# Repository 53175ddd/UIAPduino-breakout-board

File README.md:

# UIAPduino Breakout Board

UIAPduino を使った開発を手助けする，ブレッドボード用のブレイクアウトボードです．

## 部品表

| 部品番号 | 部品名 | 定数等 | リンク |
|----|----|----|----|
| C1 | コンデンサ | 0.22uF | [108146](<https://akizukidenshi.com/catalog/g/g108146/>) |
| C2 | コンデンサ | 0.1uF | [110147](<https://akizukidenshi.com/catalog/g/g110147/>) |
| C3 | コンデンサ | 22uF | [117899](<https://akizukidenshi.com/catalog/g/g117899/>) |
| C4 | コンデンサ | 10uF | [110590](<https://akizukidenshi.com/catalog/g/g110590/>) |
| D1 | ダイオード | 1N4148 | [100941](<https://akizukidenshi.com/catalog/g/g100941/>) |
| J1 | ピンヘッダ | 20P | [116590](<https://akizukidenshi.com/catalog/g/g116590/>) |
| J2 | ピンソケット | 20P | [103077](<https://akizukidenshi.com/catalog/g/g103077/>) |
| J3 | DC ジャック | 55-25 | [106568](<https://akizukidenshi.com/catalog/g/g106568/>) |
| U1 | USB-UART 変換 | FT234X モジュール | [108461](<https://akizukidenshi.com/catalog/g/g108461/>) |
| U2 | マイコン | UIAPduino Pro Micro CH32V003 | [ssci.to/9914](<https://www.switch-science.com/products/9914>) |
| U3 | 電源レギュレータ | NJM7805 | [108678](<https://akizukidenshi.com/catalog/g/g108678/>) |

## アートワークイメージ

[KiCanvas](https://kicanvas.org) でアートワークを見ることができます．  
<https://kicanvas.org/?repo=https%3A%2F%2Fgithub.com%2F53175ddd%2FUIAPduino-breakout-board>

---

This work is licensed under <a href="https://creativecommons.org/licenses/by-sa/4.0/">CC BY-SA 4.0</a>

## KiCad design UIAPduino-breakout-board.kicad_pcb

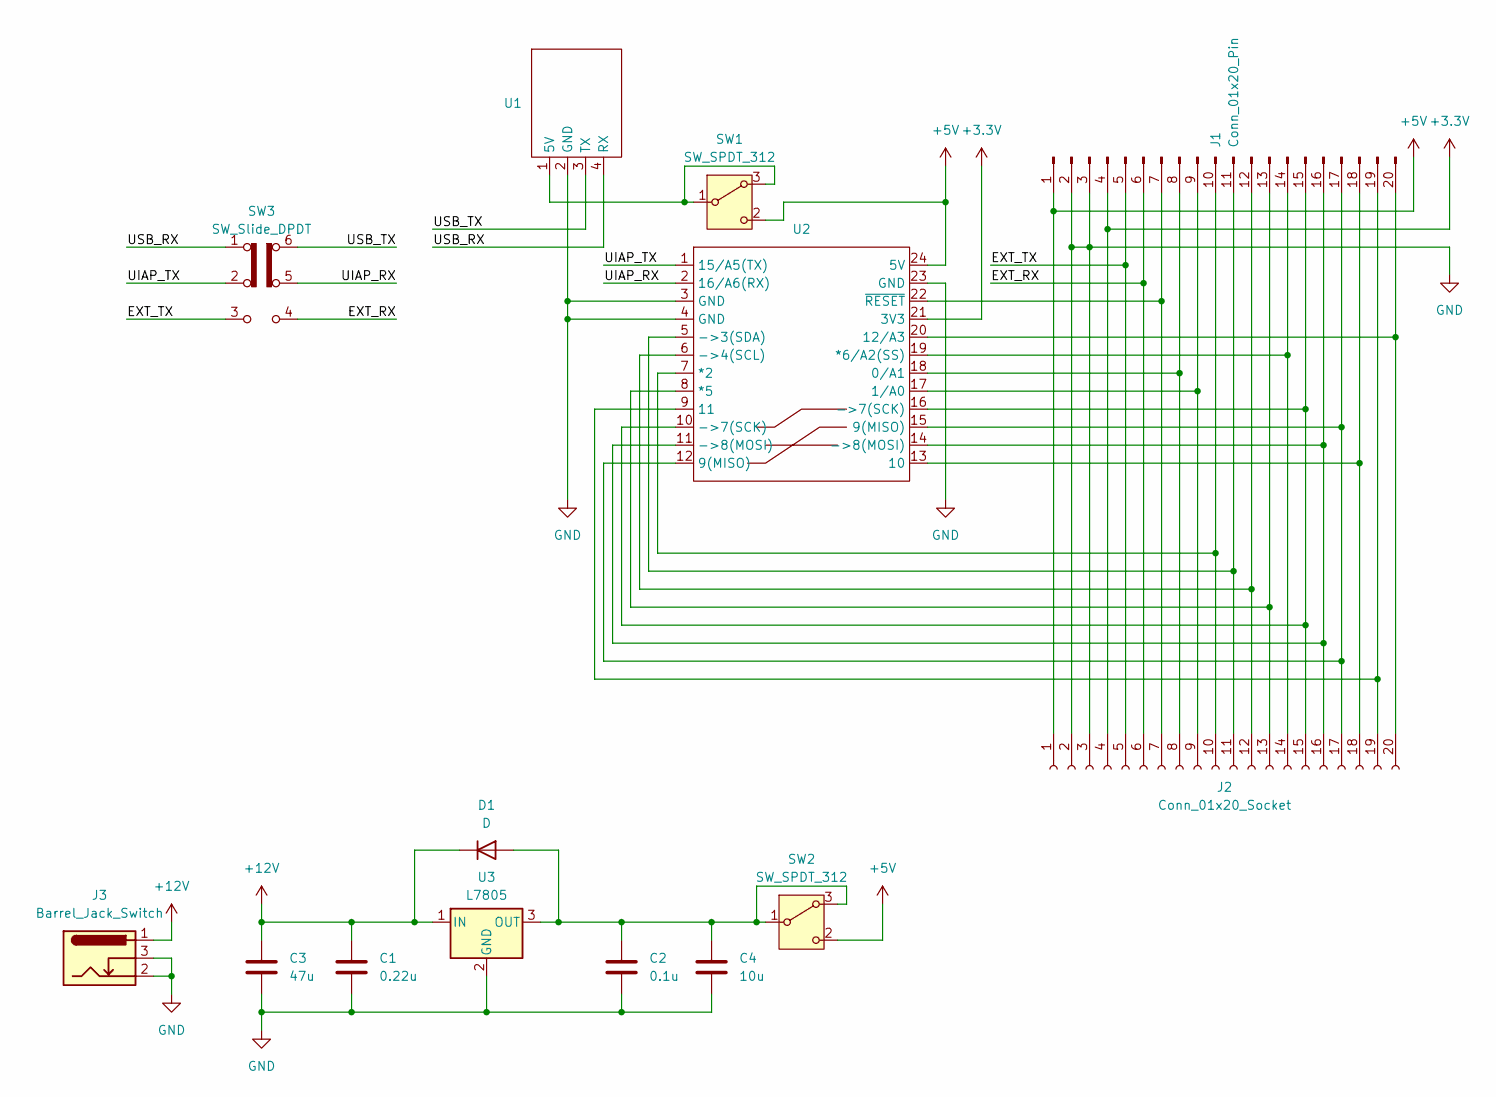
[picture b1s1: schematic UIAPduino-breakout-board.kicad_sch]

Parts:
C1: 0.22u; C_Disc_D5.0mm_W2.5mm_P5.00mm
C2: 0.1u; C_Disc_D5.0mm_W2.5mm_P5.00mm
C3: 47u; CP_Radial_D5.0mm_P2.00mm
C4: 10u; CP_Radial_D4.0mm_P1.50mm
D1: D; D_A-405_P7.62mm_Horizontal
J1: Conn_01x20_Pin; PinHeader_1x20_P2.54mm_Vertical
J2: Conn_01x20_Socket; PinSocket_1x20_P2.54mm_Vertical
J3: Barrel_Jack_Switch; BarrelJack_Horizontal
SW1, SW2: SW_SPDT_312; SW_Slide-03_Wuerth-WS-SLTV_10x2.5x6.4_P2.54mm
SW3: SW_Slide_DPDT; SW_CK_JS202011CQN_DPDT_Straight
U1: FT234X
U2: UIAPDUINO-PRO-MICRO-CH32V003-V1DOT4
U3: L7805; TO-220F-3_Vertical

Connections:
+3.3V: J1.4, J2.4, U2.21 (3V3)
+5V: J1.1, J2.1, SW1.2 (C), SW2.2 (C), U2.24 (5V)
+12V: C1.1, C3.1, D1.1 (K), J3.1, U3.1 (IN)
/EXT_RX: J1.6, J2.6, SW3.4 (A)
/EXT_TX: J1.5, J2.5, SW3.3 (C)
/UIAP_RX: SW3.5 (B), U2.2 (16/A6(RX))
/UIAP_TX: SW3.2 (B), U2.1 (15/A5(TX))
/USB_RX: SW3.1 (A), U1.4 (RX)
/USB_TX: SW3.6 (C), U1.3 (TX)
GND: C1.2, C2.2, C3.2, C4.2, J1.2, J1.3, J2.2, J2.3, J3.2, J3.3, U1.2 (GND), U2.3 (GND), U2.4 (GND), U2.23 (GND), U3.2 (GND)
unnamed: C2.1, C4.1, D1.2 (A), SW2.1 (B), SW2.3 (A), U3.3 (OUT)
unnamed: J1.7, J2.7, U2.22 (~RESET)
unnamed: J1.8, J2.8, U2.18 (0/A1)
unnamed: J1.9, J2.9, U2.17 (1/A0)
unnamed: J1.10, J2.10, U2.7 (*2)
unnamed: J1.11, J2.11, U2.5 (->3(SDA))
unnamed: J1.12, J2.12, U2.6 (->4(SCL))
unnamed: J1.13, J2.13, U2.8 (*5)
unnamed: J1.14, J2.14, U2.19 (*6/A2(SS))
unnamed: J1.15, J2.15, U2.10 (->7(SCK)), U2.16 (->7(SCK))
unnamed: J1.16, J2.16, U2.11 (->8(MOSI)), U2.14 (->8(MOSI))
unnamed: J1.17, J2.17, U2.12 (9(MISO)), U2.15 (9(MISO))
unnamed: J1.18, J2.18, U2.13 (10)
unnamed: J1.19, J2.19, U2.9 (11)
unnamed: J1.20, J2.20, U2.20 (12/A3)
unnamed: SW1.1 (B), SW1.3 (A), U1.1 (5V)

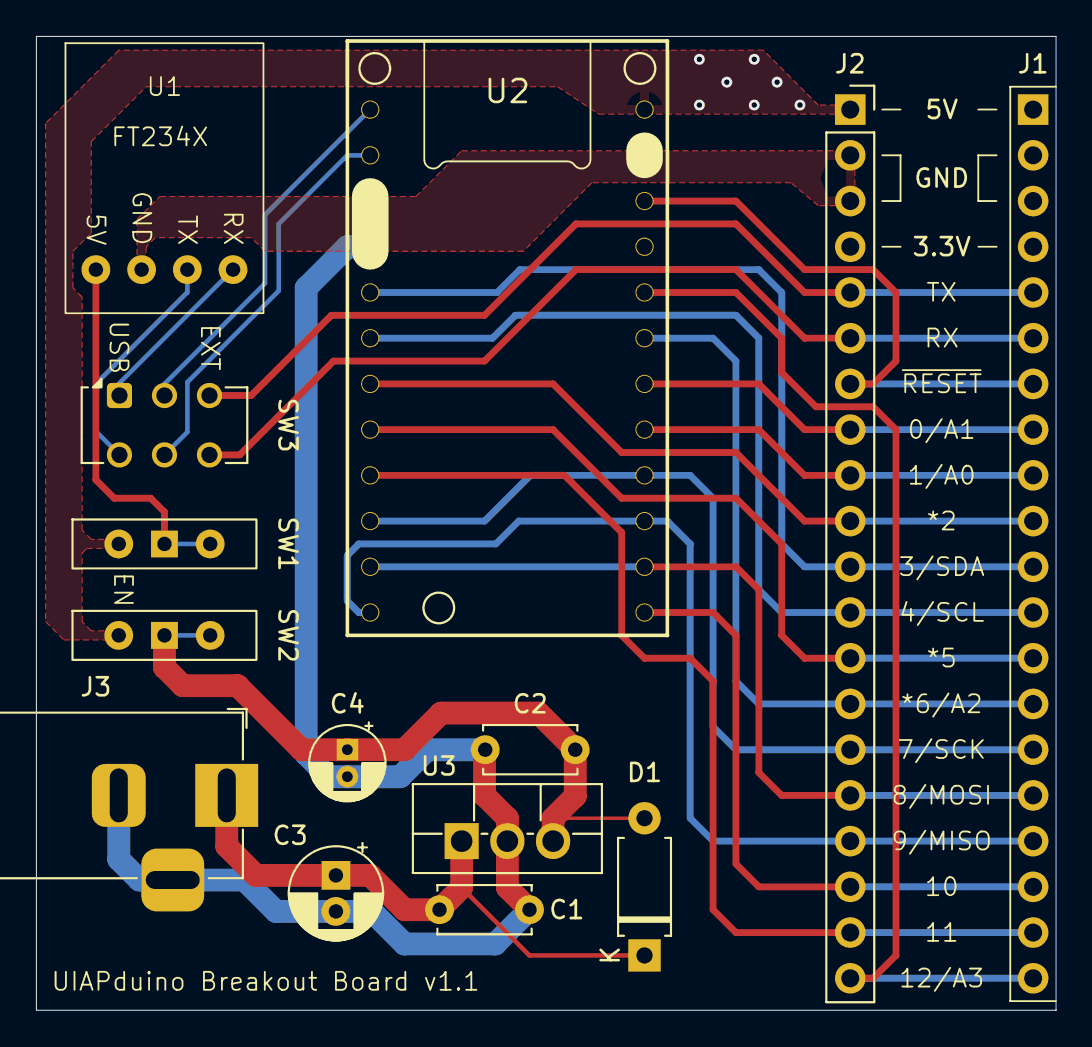
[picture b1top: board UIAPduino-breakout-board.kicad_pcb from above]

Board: 2 copper layers, 56.6 x 54.1 mm, 14 parts (1 on the bottom side), 26 nets.

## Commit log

2026-02-19 License
2026-02-19 README
2026-02-19 kicad pj
2026-02-19 UIAPduino の sym と fp
2026-02-19 USB シリアル変換器
2026-02-19 FP 割り当て
2026-02-19 大まかな配置
2026-02-19 回路修正
2026-02-19 reload
2026-02-19 信号線を配線
2026-02-19 電源配置を変更
2026-02-19 配線をいい感じに
2026-02-19 だいたい仕上げた
2026-02-19 電源入力回路追加
2026-02-19 JP の向きを反転
2026-02-19 7805 の FP 変更
2026-02-19 電源回路追加
2026-02-19 外形とシルクを調整
2026-02-19 readme に部品表を追加
2026-02-22 パターン修正
2026-02-22 update gitignore
2026-02-22 製造データ出力
2026-03-02 地味改良
2026-03-03 基板外形調整
2026-03-03 ベタ塗り直し
2026-03-14 ジャンパをスイッチに変更
2026-03-14 なくていい配線を削除
2026-03-14 UART 接続先切り替え用スイッチを追加
2026-03-14 電源配線ちょい弄り
2026-03-14 シルク調整
2026-03-14 3.3V の引出し線の調整
2026-03-14 ベタの形が気に食わん
2026-03-22 配線を見直して via を除去
2026-03-22 配線修正
2026-03-22 なくしてた接続を戻した
2026-03-25 シルク印刷の調整
2026-03-25 余計な迂回を解消
2026-03-28 Add artwork image section to README
    Added a section for artwork images with a link to KiCanvas.
2026-04-04 微妙な配線修正
2026-04-25 5V 部分をちょっと変更
